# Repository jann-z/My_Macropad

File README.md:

# My Macropad

Welcome to my Macropad project! 
This repository contains all the design files for the case, the PCB, and the firmware necessary to build this custom keypad.

## Project Overview

This project is a fully custom-designed macropad built around the Seeed XIAO RP2040 microcontroller.
Designed as part of the Hack Club submission, the goal was to create a functional, budget-friendly input device.

The device features are 6 mechanical switches for a tactile typing experience.
The PCB was created using KiCad, keeping the layout clean and efficient on a 2-layers.

Running on QMK firmware, the pad is fully programmable, allowing users to customize keymaps for gaming, coding shortcuts, or media control.
It serves as both a practical tool and a showcase of custom hardware design.

The case is version 2 because without the "bump" (inspired by Google Pixel camera-bump), the rotary encoder wouldn't fit.

## Design & Visuals

Per the submission requirements, here are the different views of the project:

### 1. The Assembled Macropad (Render)
A 3D render of the complete assembly (Case + PCB):

### 2. Case Design
The 3D printed Case and Top:

### 3. PCB Layout
A view of the PCB routing:

### 4. Schematic
The electronic schematic for the device:

---

## Default keymap

* **SW1** Copy
* **SW2** Undo
* **SW3** Clipboard (Paste)
* **SW4** Explorer
* **SW5** Cut
* **SW6** Taskmanager

### Rotary Encoder (EC11)

Modes are changet by pressing the switch of the Encoder (SW7):

* **Mode 1** Volume
* **Mode 2** RGB Brightness
* **Mode 3** RGB Pattern

## Bill of Materials (BOM)

Here are the parts required to build this macropad:

| Component | Quantity | Description / Notes |
| :--- | :---: | :--- |
| Seeed XIAO RP2040 | 1 | The main microcontroller |
| Cherry MX Switches | 6 | (or compatible clones) |
| Keycaps | 6 | Compatible with chosen switches |
| SK6812 MINI-E LED | 6 | (or fitting neopixel-leds) |
| EC11 Rotary encoder | 1 | For Volume, Brightness, ect. |
| 3D Print Filament | - | PLA or PETG for the case |
| Screws | 4 | M3x16mm for assembly (Thread trough Plastic) |

---

## Features

* **MCU:** Seeed XIAO RP2040
* **Firmware:** QMK
* **Connectivity:** USB-C

## License
This project is open source.

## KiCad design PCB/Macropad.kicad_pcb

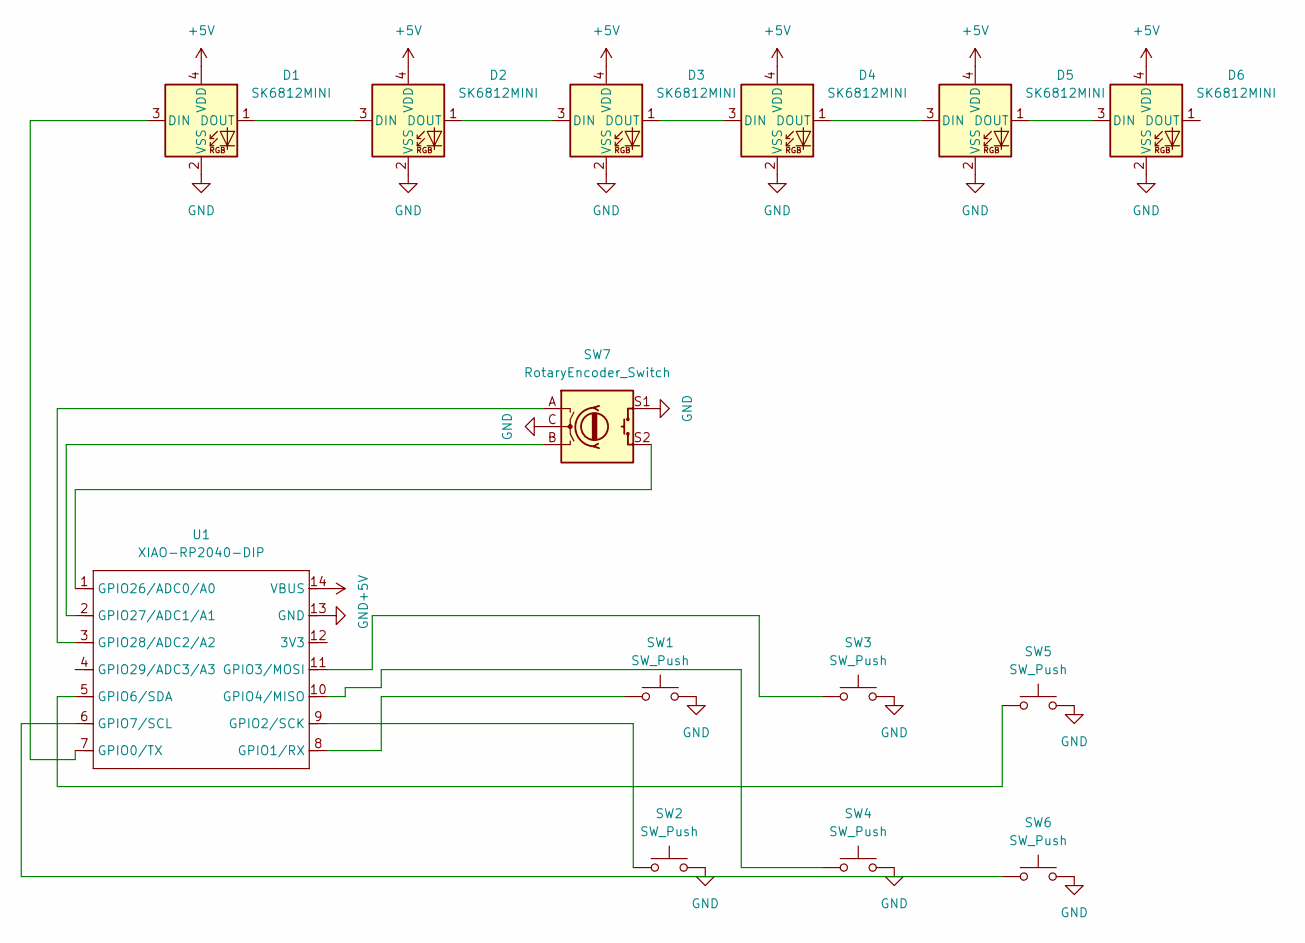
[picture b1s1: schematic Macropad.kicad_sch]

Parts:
D1, D2, D3, D4, D5, D6: SK6812MINI; LED_SK6812MINI_PLCC4_3.5x3.5mm_P1.75mm
SW1, SW2, SW3, SW4, SW5, SW6: SW_Push; SW_Cherry_MX_1.00u_PCB
SW7: RotaryEncoder_Switch; RotaryEncoder_Alps_EC11E-Switch_Vertical_H20mm
U1: XIAO-RP2040-DIP; MCU_Seeed_ESP32C3

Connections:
+5V: D1.4 (VDD), D2.4 (VDD), D3.4 (VDD), D4.4 (VDD), D5.4 (VDD), D6.4 (VDD), U1.14 (VBUS)
GND: D1.2 (VSS), D2.2 (VSS), D3.2 (VSS), D4.2 (VSS), D5.2 (VSS), D6.2 (VSS), SW1.2, SW2.2, SW3.2, SW4.2, SW5.2, SW6.2, SW7.C, SW7.S1, U1.13 (GND)
unnamed: D1.3 (DIN), U1.7 (GPIO0/TX)
unnamed: D1.1 (DOUT), D2.3 (DIN)
unnamed: D2.1 (DOUT), D3.3 (DIN)
unnamed: D3.1 (DOUT), D4.3 (DIN)
unnamed: D4.1 (DOUT), D5.3 (DIN)
unnamed: D5.1 (DOUT), D6.3 (DIN)
unnamed: SW1.1, U1.8 (GPIO1/RX)
unnamed: SW2.1, U1.9 (GPIO2/SCK)
unnamed: SW3.1, U1.11 (GPIO3/MOSI)
unnamed: SW4.1, U1.10 (GPIO4/MISO)
unnamed: SW5.1, U1.5 (GPIO6/SDA)
unnamed: SW6.1, U1.6 (GPIO7/SCL)
unnamed: SW7.S2, U1.1 (GPIO26/ADC0/A0)
unnamed: SW7.B, U1.2 (GPIO27/ADC1/A1)
unnamed: SW7.A, U1.3 (GPIO28/ADC2/A2)

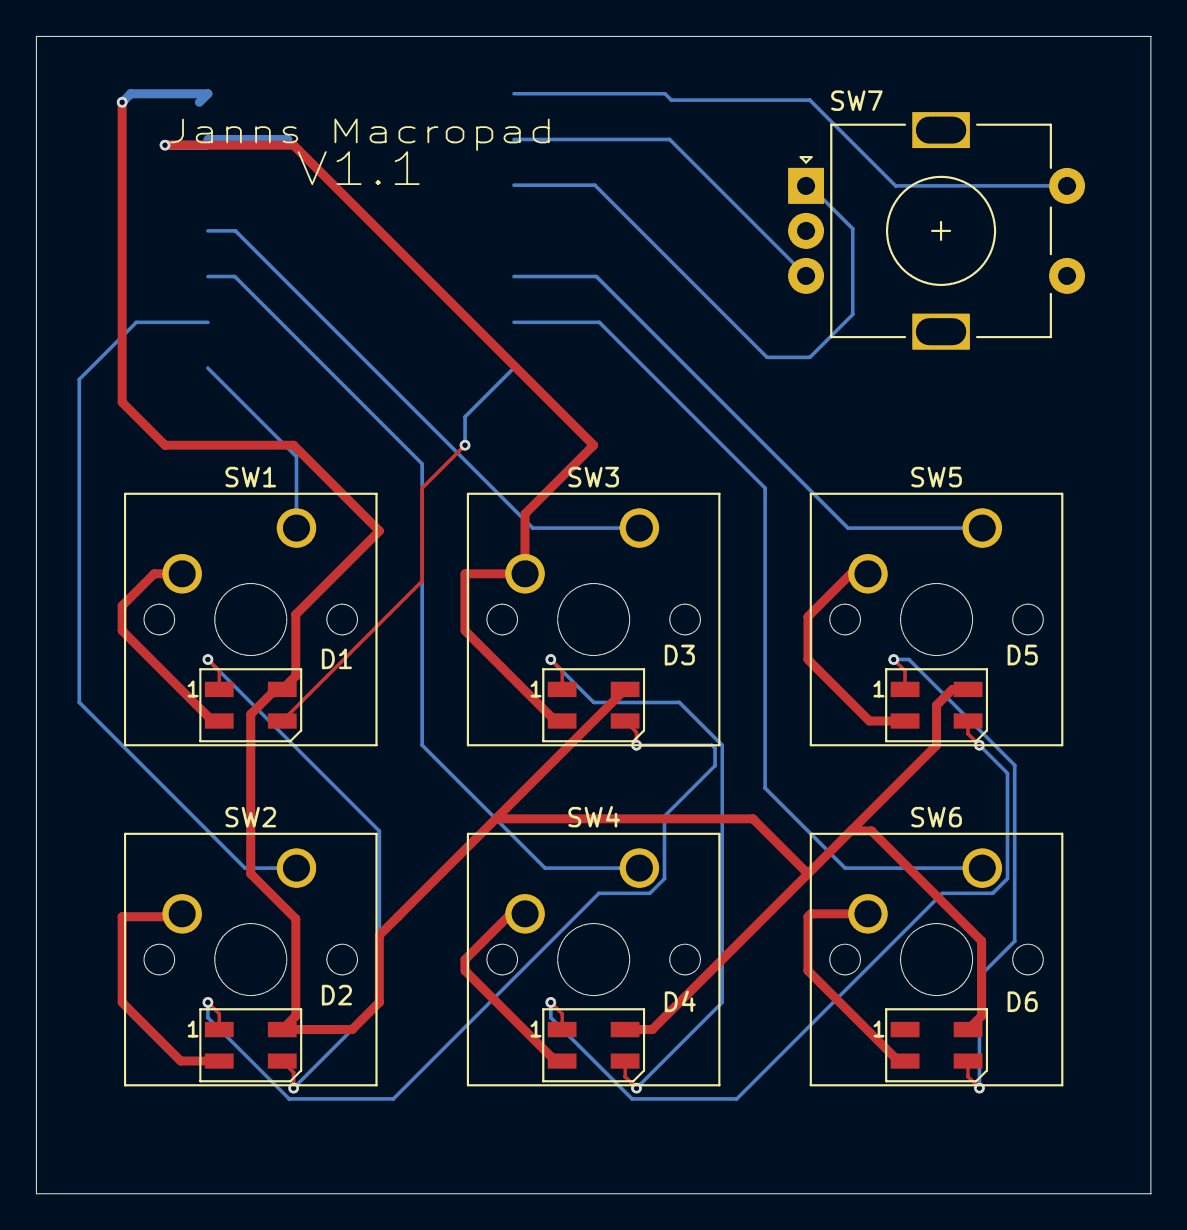
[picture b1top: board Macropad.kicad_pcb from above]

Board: 2 copper layers, 61.9 x 64.3 mm, 14 parts (1 on the bottom side), 17 nets.

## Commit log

2025-12-24 Add Hello to new txt file
2025-12-24 Added all Macropad files
2025-12-26 Firmware Finished
2025-12-26 Updated Filesystem
    For Hackclub Submission Guidelines
2025-12-26 Added README
    Added detailed project description, visuals, BOM, features, and license information.
2025-12-26 Update README
    Removed placeholder text for image path in README.
2025-12-26 Added Images to Repo
2025-12-26 Better README
    Updated the description of the case design section.
2025-12-26 Replaced Bad Pictures
2025-12-26 Add default keymap to README
    Added default keymap section with key functions.
2025-12-27 Document Rotary Encoder modes in README
    Added section about Rotary Encoder modes to README.
2025-12-27 Fix typo in Rotary Encoder modes description
    Corrected a typo in the modes description for the Rotary Encoder.
2025-12-27 Added 2. Screenshot
2025-12-27 Add second case assembly image to README
2025-12-27 Fixed Faital Error with GND plate
2025-12-27 Fixed Faital Error with PCB Gnd Plate
2026-01-07 Added the final gerber files I sent to JLCPCB
2026-01-07 Added a printable 3mf File
2026-01-13 New Version of top case
    (inspired by Google Pixel camera-bump)
2026-01-13 added a 3mf for esyer printing
2026-01-13 Clarify case version 2 design rationale
    Added explanation for case version 2 regarding rotary encoder fit.
